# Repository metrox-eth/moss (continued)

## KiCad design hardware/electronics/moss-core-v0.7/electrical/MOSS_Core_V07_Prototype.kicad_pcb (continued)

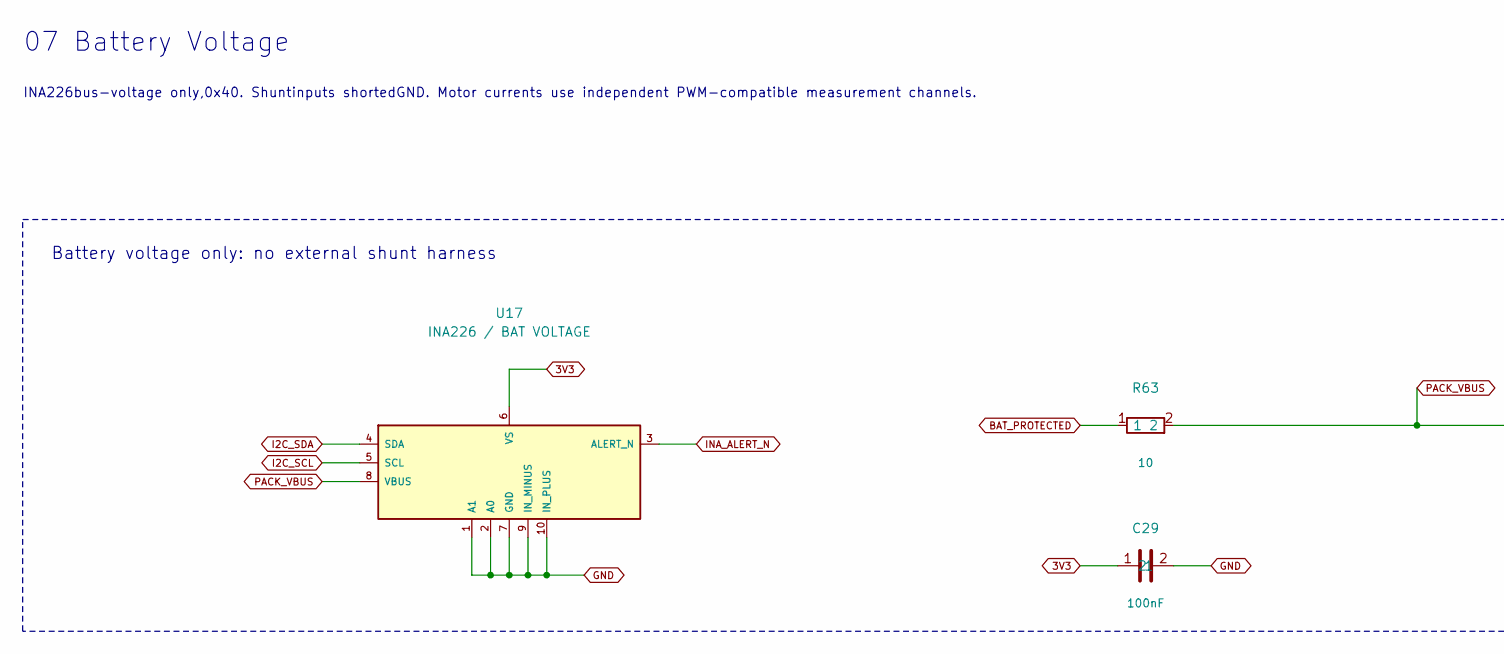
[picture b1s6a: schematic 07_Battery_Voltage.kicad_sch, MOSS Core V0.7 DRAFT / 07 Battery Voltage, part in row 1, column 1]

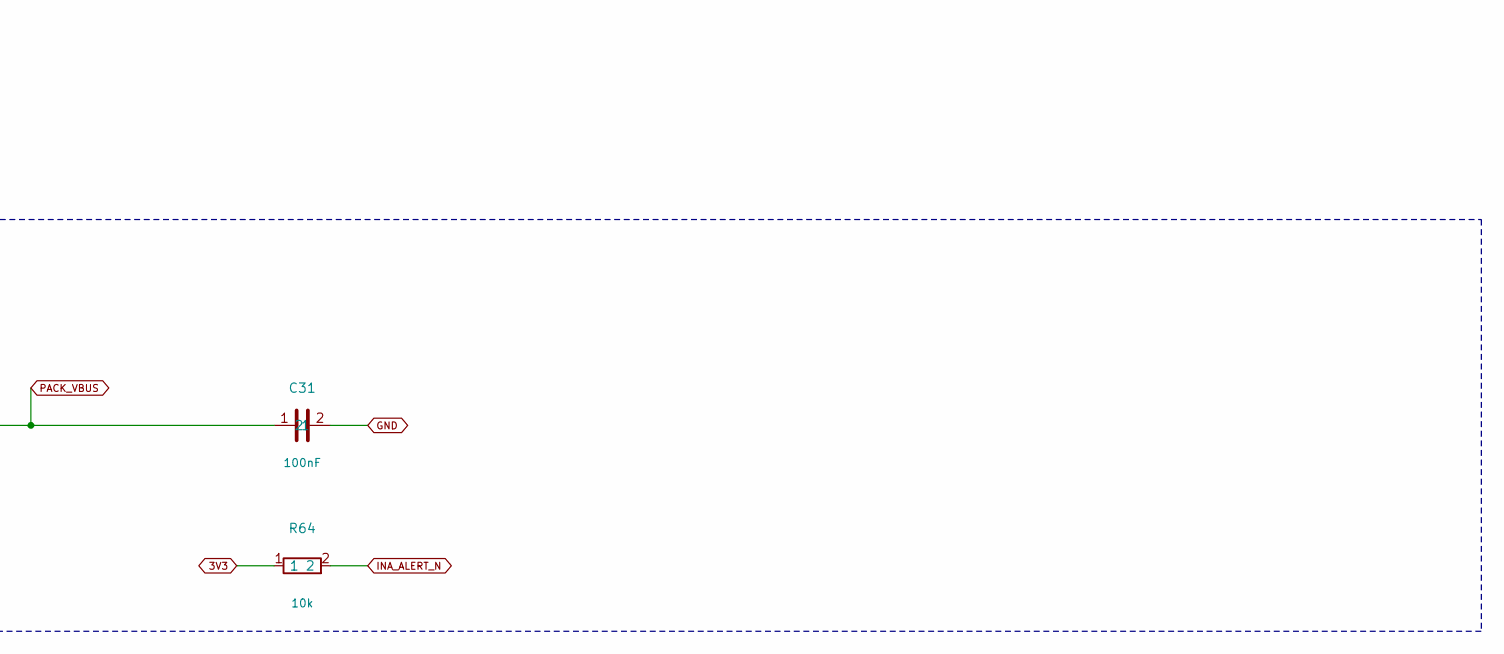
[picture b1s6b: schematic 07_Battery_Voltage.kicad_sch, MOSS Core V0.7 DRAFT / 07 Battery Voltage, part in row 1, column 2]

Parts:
C29: 100nF; Capacitor_SMD_C_0603_1608Metric; MPN GRM188R71C104KA01D
C31: 100nF; Capacitor_SMD_C_0603_1608Metric; MPN GRM188R71H104KA93D
R63: 10; Resistor_SMD_R_0603_1608Metric; MPN RC0603FR-0710RL
R64: 10k; Resistor_SMD_R_0603_1608Metric; MPN RC0603FR-0710KL
U17: INA226 / BAT VOLTAGE; Package_SO_MSOP-10_3x3mm_P0.5mm; MPN INA226AIDGSR

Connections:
3V3: C29.1, R64.1, U17.6 (VS); also elsewhere on the board
BAT_PROTECTED: R63.1; also elsewhere on the board
GND: C29.2, C31.2, U17.1 (A1), U17.2 (A0), U17.7 (GND), U17.9 (IN_MINUS), U17.10 (IN_PLUS); also elsewhere on the board
I2C_SCL: U17.5 (SCL); also elsewhere on the board
I2C_SDA: U17.4 (SDA); also elsewhere on the board
INA_ALERT_N: R64.2, U17.3 (ALERT_N)
PACK_VBUS: C31.1, R63.2, U17.8 (VBUS)

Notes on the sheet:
07 Battery Voltage
INA226bus-voltage only,0x40. Shuntinputs shortedGND. Motor currents use independent PWM-compatible measurement channels.
Battery voltage only: no external shunt harness

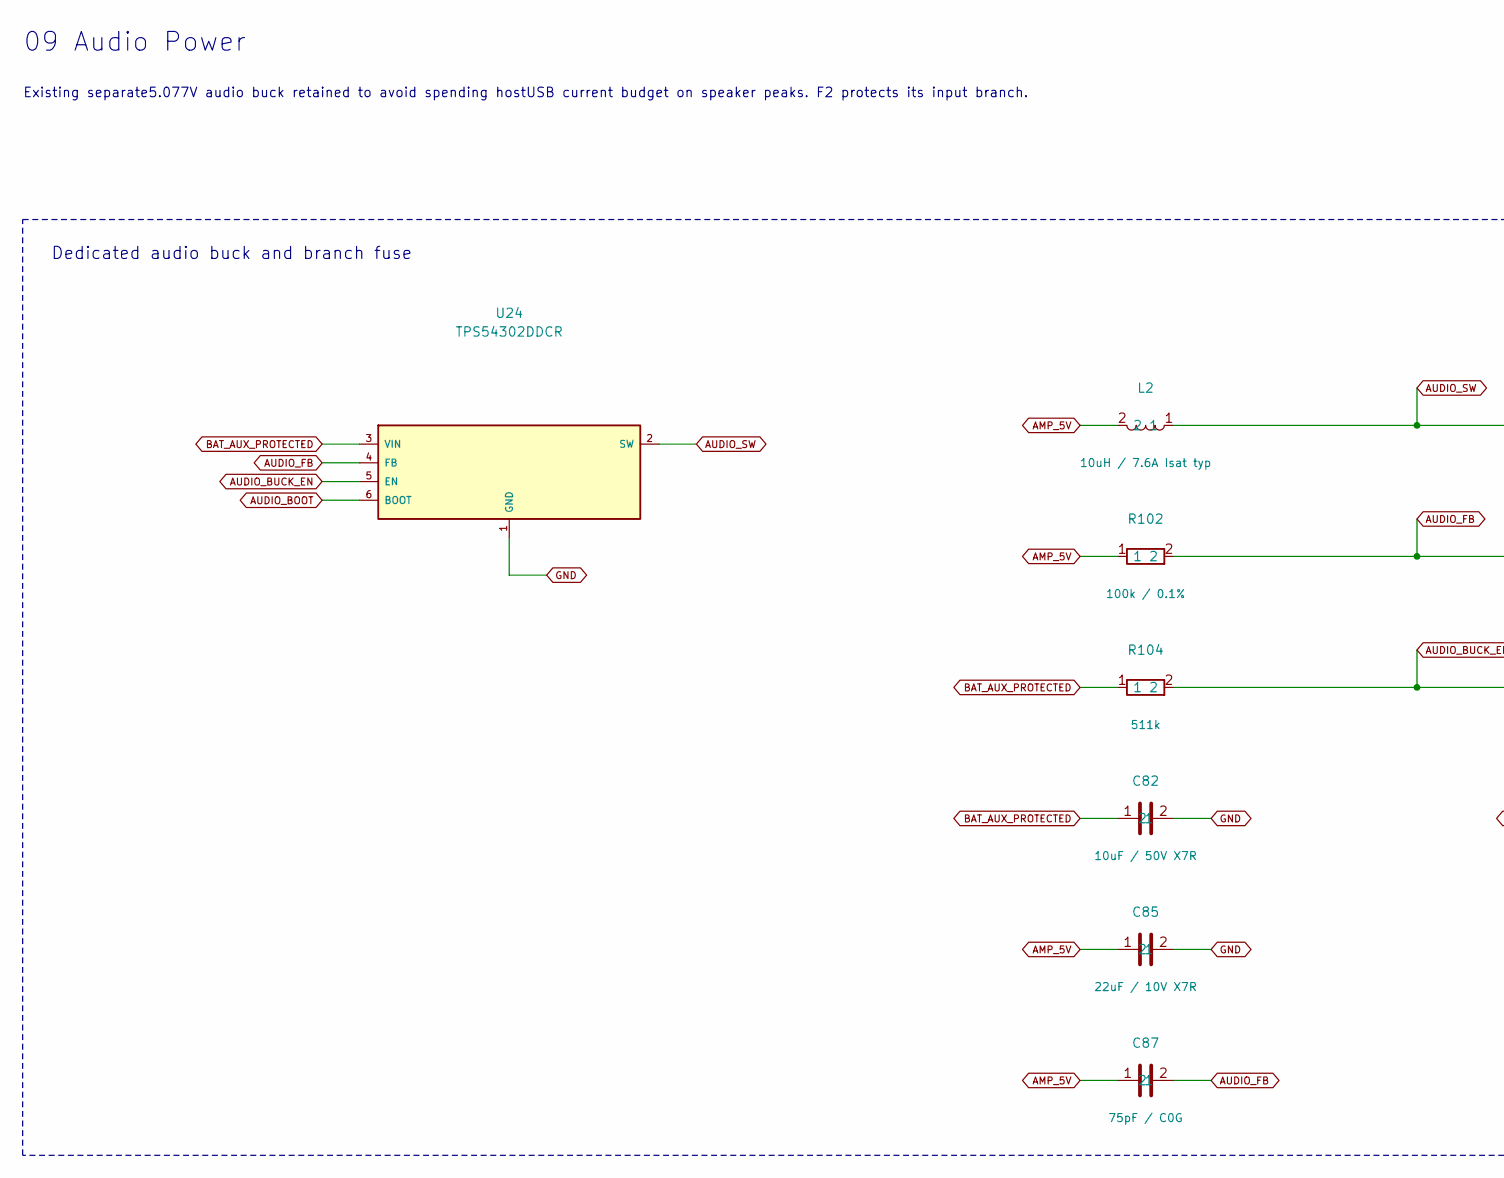
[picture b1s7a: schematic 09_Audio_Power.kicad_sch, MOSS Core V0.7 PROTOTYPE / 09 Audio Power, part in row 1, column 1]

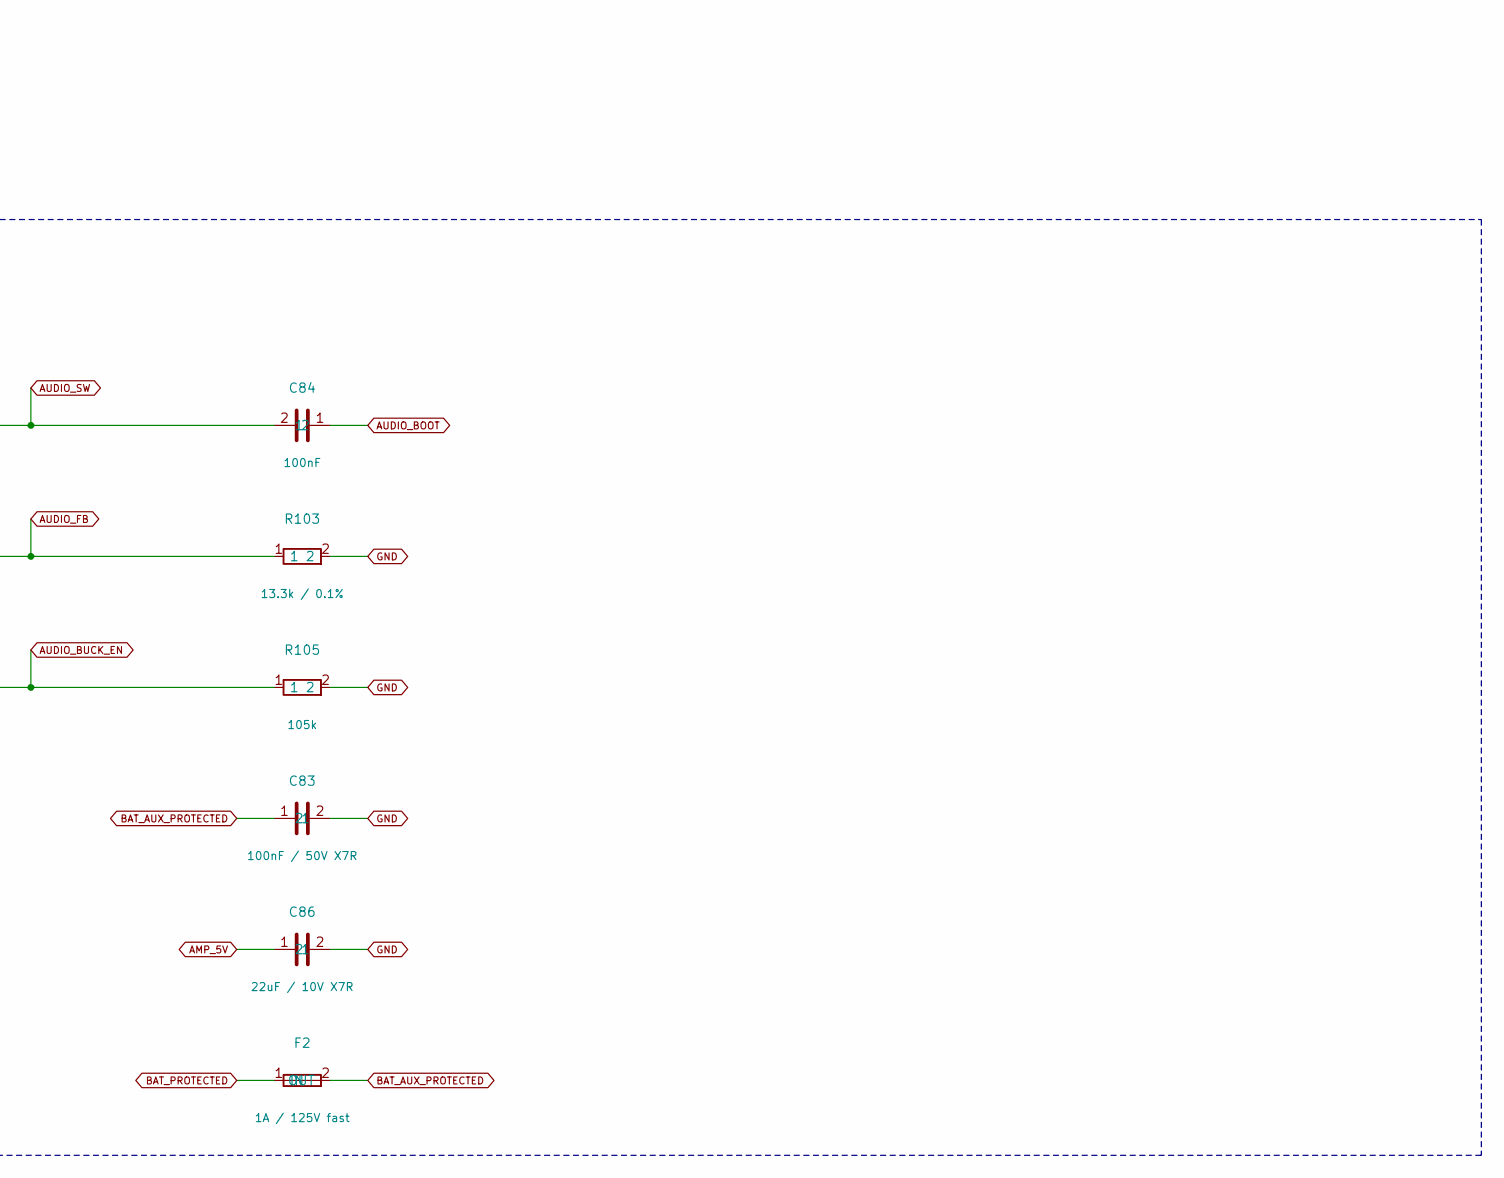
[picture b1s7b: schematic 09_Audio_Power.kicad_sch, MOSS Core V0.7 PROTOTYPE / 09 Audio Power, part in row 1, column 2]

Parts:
C82: 10uF / 50V X7R; Capacitor_SMD_C_1210_3225Metric; MPN GRM32ER71H106KA12L
C83: 100nF / 50V X7R; Capacitor_SMD_C_0805_2012Metric; MPN C0805C104K5RACTU
C84: 100nF; Capacitor_SMD_C_0603_1608Metric; MPN GRM188R71C104KA01D
C85, C86: 22uF / 10V X7R; Capacitor_SMD_C_1206_3216Metric; MPN GRM31CR71A226KE15L
C87: 75pF / C0G; Capacitor_SMD_C_0603_1608Metric; MPN GRM1885C1H750JA01D
F2: 1A / 125V fast; Fuse_Littelfuse_0451_Nano2; MPN 0451001.MRL
L2: 10uH / 7.6A Isat typ; Inductor_SMD_L_Bourns_SRP6060FA; MPN SRP6060FA-100M
R102: 100k / 0.1%; Resistor_SMD_R_0603_1608Metric; MPN RT0603BRD07100KL
R103: 13.3k / 0.1%; Resistor_SMD_R_0603_1608Metric; MPN RT0603BRD0713K3L
R104: 511k; Resistor_SMD_R_0603_1608Metric; MPN RC0603FR-07511KL
R105: 105k; Resistor_SMD_R_0603_1608Metric; MPN RC0603FR-07105KL
U24: TPS54302DDCR; Package_TO_SOT_SMD_SOT-23-6; MPN TPS54302DDCR

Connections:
AMP_5V: C85.1, C86.1, C87.1, L2.2, R102.1; also elsewhere on the board
AUDIO_BOOT: C84.1, U24.6 (BOOT)
AUDIO_BUCK_EN: R104.2, R105.1, U24.5 (EN)
AUDIO_FB: C87.2, R102.2, R103.1, U24.4 (FB)
AUDIO_SW: C84.2, L2.1, U24.2 (SW)
BAT_AUX_PROTECTED: C82.1, C83.1, F2.2 (OUT), R104.1, U24.3 (VIN)
BAT_PROTECTED: F2.1 (IN); also elsewhere on the board
GND: C82.2, C83.2, C85.2, C86.2, R103.2, R105.2, U24.1 (GND); also elsewhere on the board

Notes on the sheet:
09 Audio Power
Existing separate5.077V audio buck retained to avoid spending hostUSB current budget on speaker peaks. F2 protects its input branch.
Dedicated audio buck and branch fuse

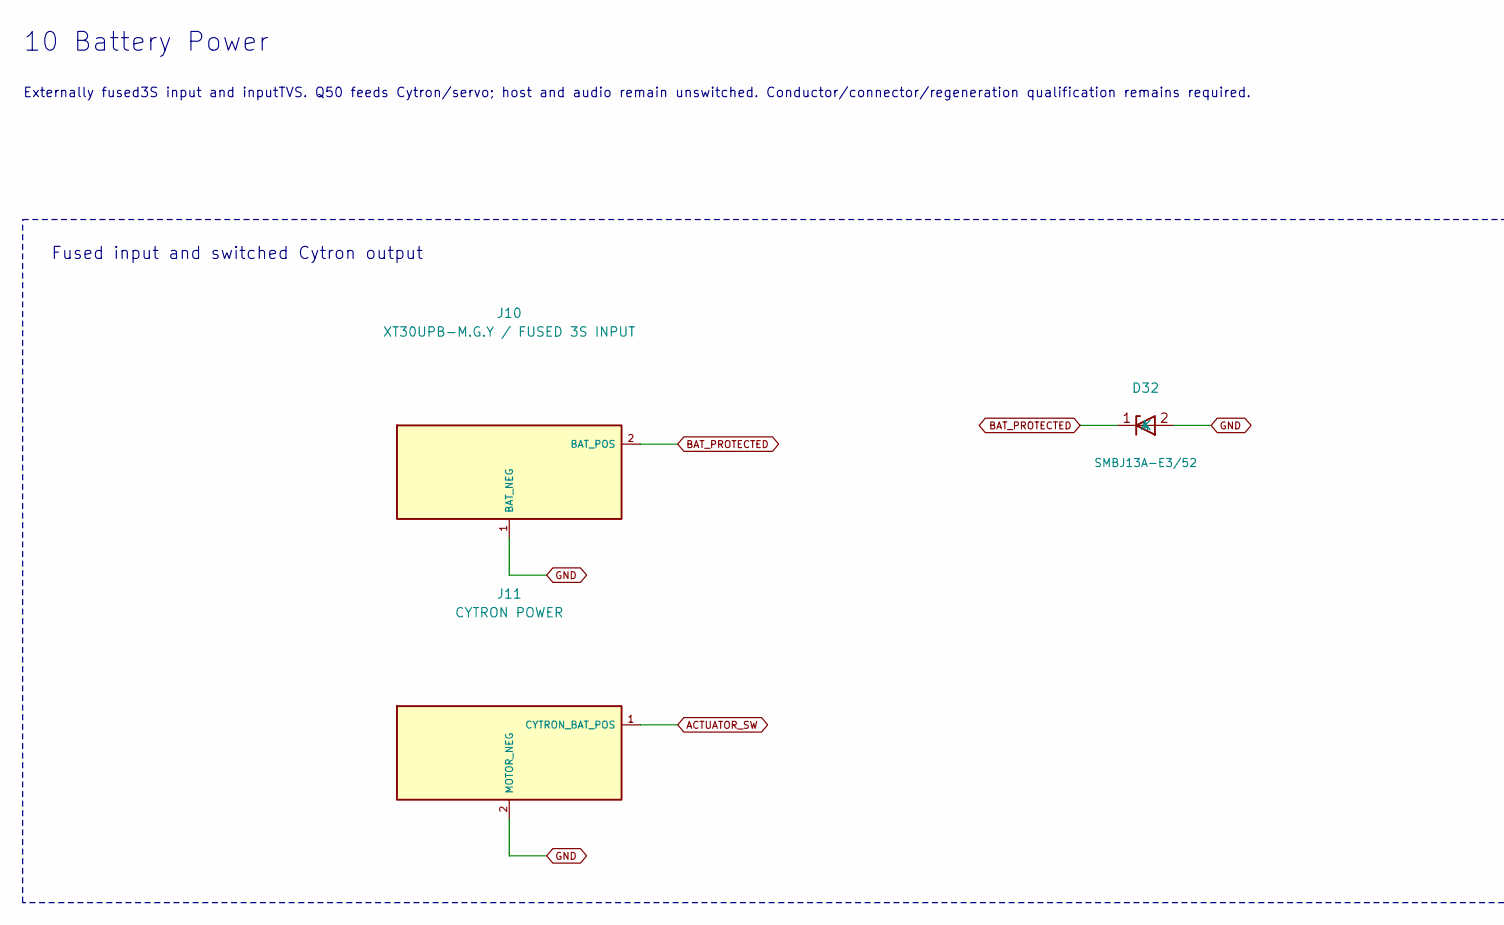
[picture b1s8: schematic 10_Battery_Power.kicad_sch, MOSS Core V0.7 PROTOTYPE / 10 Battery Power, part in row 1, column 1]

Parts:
D32: SMBJ13A-E3/52; Diode_SMD_D_SMB; MPN SMBJ13A-E3/52
J10: XT30UPB-M.G.Y / FUSED 3S INPUT; Connector_AMASS_AMASS_XT30UPB-M_1x02_P5.0mm_Vertical; MPN XT30UPB-M.G.Y
J11: CYTRON POWER; TerminalBlock_Phoenix_TerminalBlock_Phoenix_MKDS-1,5-2-5.08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; MPN 1715721

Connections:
ACTUATOR_SW: J11.1 (CYTRON_BAT_POS); also elsewhere on the board
BAT_PROTECTED: D32.1 (K), J10.2 (BAT_POS); also elsewhere on the board
GND: D32.2 (A), J10.1 (BAT_NEG), J11.2 (MOTOR_NEG); also elsewhere on the board

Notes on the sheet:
10 Battery Power
Externally fused3S input and inputTVS. Q50 feeds Cytron/servo; host and audio remain unswitched. Conductor/connector/regeneration qualification remains required.
Fused input and switched Cytron output

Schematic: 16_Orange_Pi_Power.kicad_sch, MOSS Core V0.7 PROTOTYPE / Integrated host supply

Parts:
C140: 220uF 10V polymer; Capacitor_SMD_CP_Elec_6.3x5.9; MPN 10SVPE220M
C141: 100nF 50V X7R; Capacitor_SMD_C_0603_1608Metric; MPN GRM188R71H104KA93D
C142: 10uF 25V X7R; Capacitor_SMD_C_1206_3216Metric; MPN GRM31CR71E106KA12L
C160: 22uF / 25V X7R; Capacitor_SMD_C_1210_3225Metric; MPN GRM32ER71E226KE15L
C162, C163, C167: 100nF / 50V X7R; Capacitor_SMD_C_0603_1608Metric; MPN GRM188R71H104KA93D
C164, C165: 22uF / 10V X7R; Capacitor_SMD_C_1206_3216Metric; MPN GRM31CR71A226KE15L
C166: 1uF / 10V; Capacitor_SMD_C_0603_1608Metric; MPN GRM188R61A105KA61D
C168: 33nF / 50V X7R; Capacitor_SMD_C_0603_1608Metric; MPN GRM188R71H333KA61D
C169: 390pF / C0G; Capacitor_SMD_C_0603_1608Metric; MPN GRM1885C1H391JA01D
F1: 3.15A / compact host input fuse; Fuse_Fuse_Littelfuse-NANO2-885; MPN 08853.15DR
J20: 5V3A OUT TO ORANGE PI; Connector_USB_USB_C_Receptacle_GCT_USB4105-xx-A_16P_TopMnt_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; MPN USB4105-GF-A
L3: 10uH; Inductor_SMD_L_Bourns_SRP6060FA; MPN SRP6060FA-100M
R200: 100k 1% 100ppm; Resistor_SMD_R_0603_1608Metric; MPN RC0603FR-07100KL
R210: 499k; Resistor_SMD_R_0603_1608Metric; MPN RC0603FR-07499KL
R211: 100k; Resistor_SMD_R_0603_1608Metric; MPN RC0603FR-07100KL
R212: 4.7; Resistor_SMD_R_0603_1608Metric; MPN RC0603FR-074R7L
R213: 53.6k; Resistor_SMD_R_0603_1608Metric; MPN RC0603FR-0753K6L
R214: 10k; Resistor_SMD_R_0603_1608Metric; MPN RC0603FR-0710KL
R215: 845k; Resistor_SMD_R_0603_1608Metric; MPN RC0603FR-07845KL
U42: TPS25810RVCR / USB-C source3A; Package_DFN_QFN_Texas_RVC0020A_WQFN-20-1EP_3x4mm_P0.5mm_EP1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; MPN TPS25810RVCR
U60: MP9447GL-Z / integrated host buck; MOSS_Power_MP9447_QFN25_3x4; MPN MP9447GL-Z

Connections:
BAT_PROTECTED: F1.1; also elsewhere on the board
GND: C140.2, C141.2, C142.2, C160.2, C162.2, C163.2, C164.2, C165.2, C166.2, C168.2, J20.A1 (GND), J20.A12 (GND), J20.B1 (GND), J20.B12 (GND), J20.SH (SHIELD), R211.2, R214.2, U42.12 (GND), U42.21 (EP), U60.1 (AGND), U60.11 (PGND), U60.12 (PGND), U60.13 (PGND), U60.14 (PGND), U60.15 (PGND), U60.16 (PGND); also elsewhere on the board
HOST_5V: C142.1, J20.A4 (VBUS), J20.A9 (VBUS), J20.B4 (VBUS), J20.B9 (VBUS), U42.14 (OUT), U42.15 (OUT)
HOST_BST: R212.1, U60.7 (BST)
HOST_BST_CAP: C167.1, R212.2
HOST_BUCK_IN: C160.1, C162.1, C163.1, F1.2, R210.1, U60.8 (IN), U60.19 (IN), U60.21 (IN), U60.22 (IN), U60.23 (IN)
HOST_CC1: J20.A5 (CC1), U42.11 (CC1)
HOST_CC2: J20.B5 (CC2), U42.13 (CC2)
HOST_CC_REF: R200.1, U42.10 (REF)
HOST_CC_REF_RTN: R200.2, U42.9 (REF_RTN)
HOST_EN: R210.2, U60.5 (EN)
HOST_FB: C169.2, R213.2, R214.1, U60.3 (FB)
HOST_FREQ: R211.1, U60.2 (FREQ)
HOST_RAMP: C169.1, R215.2
HOST_SS: C168.1, U60.4 (SS)
HOST_SW: C167.2, L3.1, R215.1, U60.9 (SW), U60.10 (SW), U60.17 (SW), U60.18 (SW), U60.24 (SW), U60.25 (SW)
HOST_VCC: C166.1, U60.20 (VCC)
V5_HOST_RAW: C140.1, C141.1, C164.1, C165.1, L3.2, R213.1, U42.2 (IN1), U42.3 (IN1), U42.4 (IN2), U42.5 (AUX), U42.6 (EN), U42.7 (CHG), U42.8 (CHG_HI)

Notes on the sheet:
INTEGRATED HOST POWER / MP9447 / ENGINEERING CANDIDATE
3S battery -> F1 -> U60/L3 -> V5_HOST_RAW -> U42 -> HOST_5V -> J20. Keep VBUS and V5 separate.

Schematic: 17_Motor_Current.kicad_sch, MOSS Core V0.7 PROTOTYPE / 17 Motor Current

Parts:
C120, C123, C126: 100n 16V X7R; Capacitor_SMD_C_0603_1608Metric; MPN C0603C104K4RACTU
C121, C124: 2.2u 16V X7R; Capacitor_SMD_C_0805_2012Metric; MPN C0805C225K4RACTU
C122, C125: 1u 16V X7R; Capacitor_SMD_C_0603_1608Metric; MPN C0603C105K4RACTU
J12: L MOTOR SENSE LOOP; TerminalBlock_Phoenix_TerminalBlock_Phoenix_MKDS-1,5-2-5.08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; MPN 1715721
J13: R MOTOR SENSE LOOP; TerminalBlock_Phoenix_TerminalBlock_Phoenix_MKDS-1,5-2-5.08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; MPN 1715721
R180, R181: 2mR 1% 5W; MOSS_V07_CSS2H_2512K_Bourns; MPN CSS2H-2512K-2L00F
R182, R183: 470R 1%; Resistor_SMD_R_0603_1608Metric; MPN CRCW0603470RFKEA
U40, U41: INA240A2PWR; Package_SO_TSSOP-8_4.4x3mm_P0.65mm; MPN INA240A2PWR
U43: ADS1115IDGSR; Package_SO_MSOP-10_3x3mm_P0.5mm; MPN ADS1115IDGSR

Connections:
3V3: C120.1, C122.1, C123.1, C125.1, C126.1, U40.5 (VS), U40.7 (REF1), U41.5 (VS), U41.7 (REF1), U43.6 (AIN2), U43.8 (VDD); also elsewhere on the board
CURRENT_L_ADC: C121.1, R182.2, U43.4 (AIN0)
CURRENT_L_RAW: R182.1, U40.8 (OUT)
CURRENT_R_ADC: C124.1, R183.2, U43.5 (AIN1)
CURRENT_R_RAW: R183.1, U41.8 (OUT)
CYTRON_L_LEAD: J12.1 (FROM_CYTRON), R180.1 (I_FROM_CYTRON), U40.2 (IN+); also elsewhere on the board
CYTRON_R_LEAD: J13.1 (FROM_CYTRON), R181.1 (I_FROM_CYTRON), U41.2 (IN+); also elsewhere on the board
GND: C120.2, C121.2, C122.2, C123.2, C124.2, C125.2, C126.2, U40.4 (GND), U40.6 (REF2), U41.4 (GND), U41.6 (REF2), U43.1 (ADDR), U43.3 (GND), U43.7 (AIN3); also elsewhere on the board
I2C_SCL: U43.10 (SCL); also elsewhere on the board
I2C_SDA: U43.9 (SDA); also elsewhere on the board
MOTOR_L_LEAD: J12.2 (TO_MOTOR), R180.2 (I_TO_MOTOR), U40.3 (IN-); also elsewhere on the board
MOTOR_R_LEAD: J13.2 (TO_MOTOR), R181.2 (I_TO_MOTOR), U41.3 (IN-); also elsewhere on the board

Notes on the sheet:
17 Motor Current
Separate left/right in-linebidirectional motor currents; two shunts andPWM-rejecting amplifiers. ValidateADCcalibration,transients and thermal performance.
Left in-line winding current
Right in-line winding current
Digital ADC and reference supply measurement

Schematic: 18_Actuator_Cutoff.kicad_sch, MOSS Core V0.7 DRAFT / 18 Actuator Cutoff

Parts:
C150, C152: 10n; Capacitor_SMD_C_0603_1608Metric; MPN GRM188R71H103KA01D
C151: 100n; Capacitor_SMD_C_0603_1608Metric; MPN GRM188R71H104KA93D
C153: 1n; Capacitor_SMD_C_0603_1608Metric; MPN GRM188R71H102KA01D
D50: BZT52C12; Diode_SMD_D_SOD-123; MPN BZT52C12-E3-08
J8: E-STOP / SIGNAL ONLY; Connector_JST_JST_SH_BM06B-SRSS-TB_1x06-1MP_P1.00mm_Vertical; MPN BM06B-SRSS-TB(LF)(SN)
Q50: SiRA99DP; Package_SO_PowerPAK_SO-8_Single; MPN SiRA99DP-T1-GE3
Q51, Q52: BSS138BK; Package_TO_SOT_SMD_SOT-23; MPN BSS138BK,215
R220, R226: 1k; Resistor_SMD_R_1206_3216Metric; MPN RC1206FR-071KL
R221: 330; Resistor_SMD_R_1206_3216Metric; MPN RC1206FR-07330RL
R222: 1k; Resistor_SMD_R_0603_1608Metric; MPN RC0603FR-071KL
R223, R227: 10k; Resistor_SMD_R_0603_1608Metric; MPN RC0603FR-0710KL
R224: 47; Resistor_SMD_R_0603_1608Metric; MPN RC0603FR-0747RL
R225: 470; Resistor_SMD_R_0603_1608Metric; MPN RC0603FR-07470RL
U50: SN74LVC1G14; Package_TO_SOT_SMD_SOT-23-5; MPN SN74LVC1G14DBVR

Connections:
3V3: C151.1, R224.1, U50.5 (VCC); also elsewhere on the board
ACTUATOR_SW: Q50.5 (D5-8_PAD), R226.1; also elsewhere on the board
ACT_GATE: C152.2, D50.2 (A), Q50.4 (G), R220.2, R221.1
ACT_POWER_ENABLE: R222.1; also elsewhere on the board
ACT_SINK_GATE: C153.1, Q51.1 (G), R222.2, R223.1
BAT_PROTECTED: C152.1, D50.1 (K), Q50.1 (S1), Q50.2 (S2), Q50.3 (S3), R220.1; also elsewhere on the board
ESTOP_ACTIVE: Q52.1 (G), R227.1, U50.4 (Y); also elsewhere on the board
ESTOP_CUT_RETURN: J8.2 (CUT_RETURN), Q51.3 (D)
ESTOP_CUT_SOURCE: J8.1 (CUT_SOURCE), R221.2
ESTOP_STATUS_RAW: C150.1, J8.6 (STATUS_RETURN), R225.1, U50.2 (A)
ESTOP_STATUS_SOURCE: J8.5 (STATUS_SOURCE), R224.2
GND: C150.2, C151.2, C153.2, J8.MP (MOUNT), Q51.2 (S), Q52.2 (S), R223.2, R225.2, R226.2, R227.2, U50.3 (GND); also elsewhere on the board
WD_RESET_N: Q52.3 (D); also elsewhere on the board

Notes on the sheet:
18 Actuator Cutoff
One physical NC opens Q50 gate sink regardless of MCU command. Second NC requests MCU reset; release requires fresh manual arming. Unknown actual button terminal orientation must be verified. Single MOSFET is not redundant or safety-certified; inrush, stored energy and regeneration require bench te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
High-side actuator switch / NC contact dominates gate
MCU arm request / default off
Two NC contacts / signal harness only
Auxiliary stop contact resets controller

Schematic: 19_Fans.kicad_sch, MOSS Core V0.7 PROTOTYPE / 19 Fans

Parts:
F3: 1A / 125V fast; Fuse_Littelfuse_0451_Nano2; MPN 0451001.MRL
J14: FAN 1 / 3S; Connector_JST_JST_XH_B2B-XH-A_1x02_P2.50mm_Vertical; MPN B2B-XH-A(LF)(SN)
J15: FAN 2 / 3S; Connector_JST_JST_XH_B2B-XH-A_1x02_P2.50mm_Vertical; MPN B2B-XH-A(LF)(SN)

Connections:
BAT_PROTECTED: F3.1 (IN); also elsewhere on the board
FAN_3S: F3.2 (OUT), J14.1 (FAN_POS), J15.1 (FAN_POS)
GND: J14.2 (FAN_NEG), J15.2 (FAN_NEG); also elsewhere on the board

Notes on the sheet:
19 Fans
Two12V nominal3010 fans,common1A fuse upstream of Q50;0.2A combined assumed,not measured. Verify XH mate/polarity,voltage/startup and wire limits.
Battery-fed fans / powered during actuator stop

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
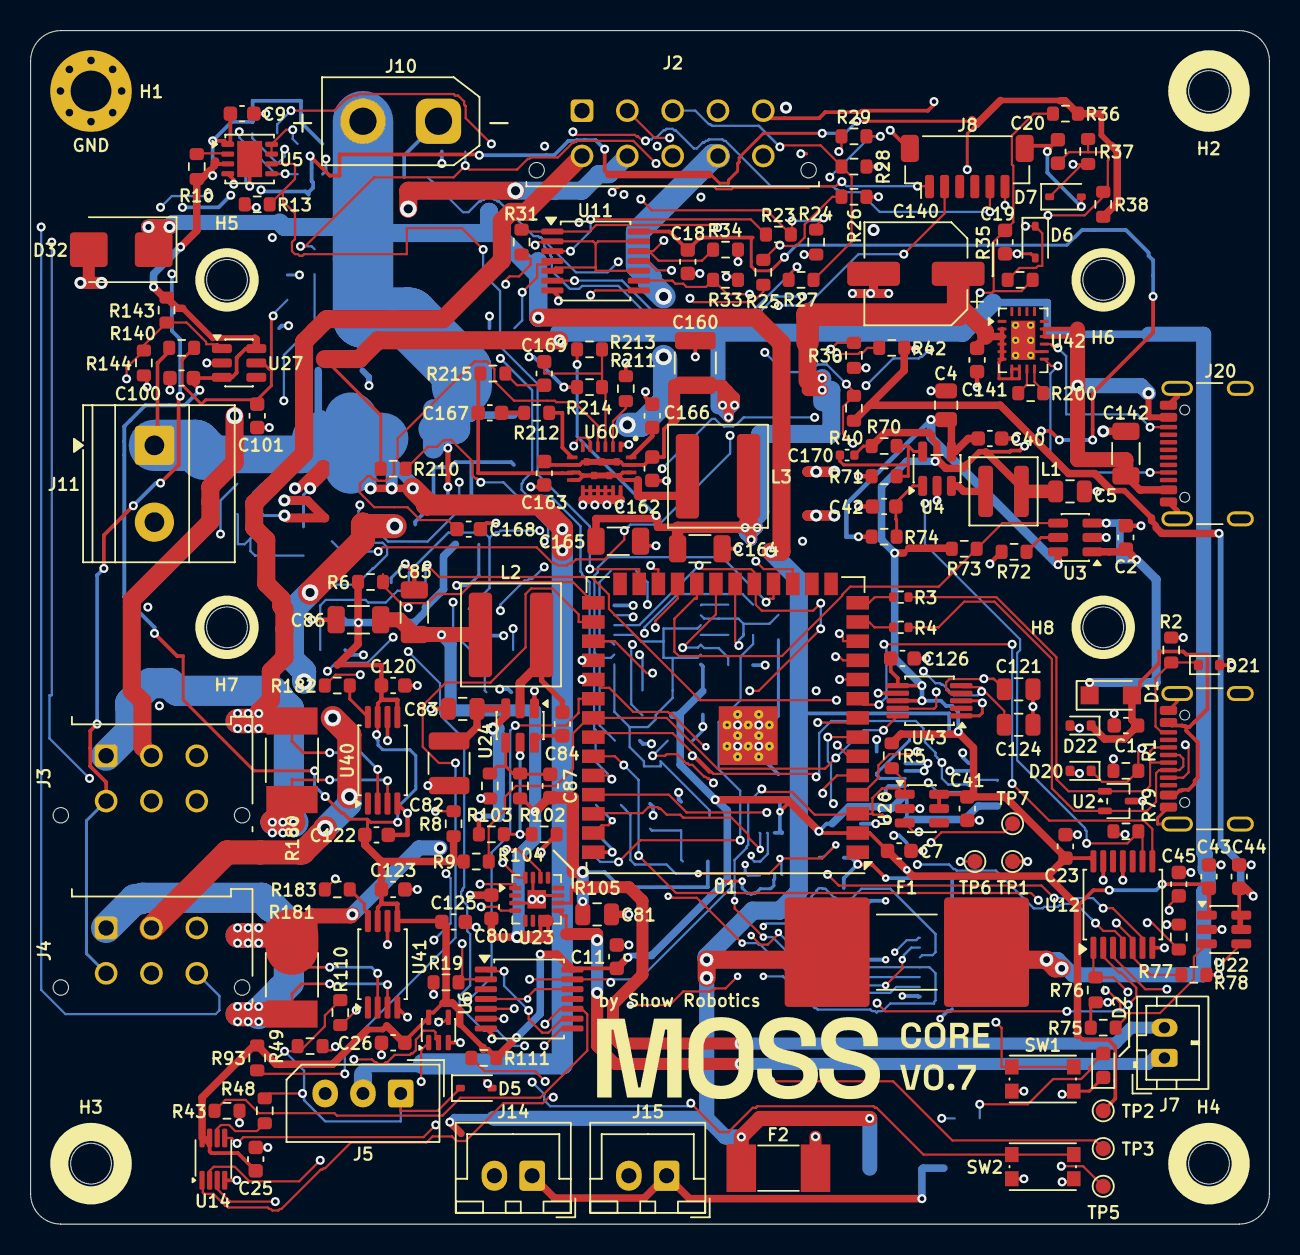
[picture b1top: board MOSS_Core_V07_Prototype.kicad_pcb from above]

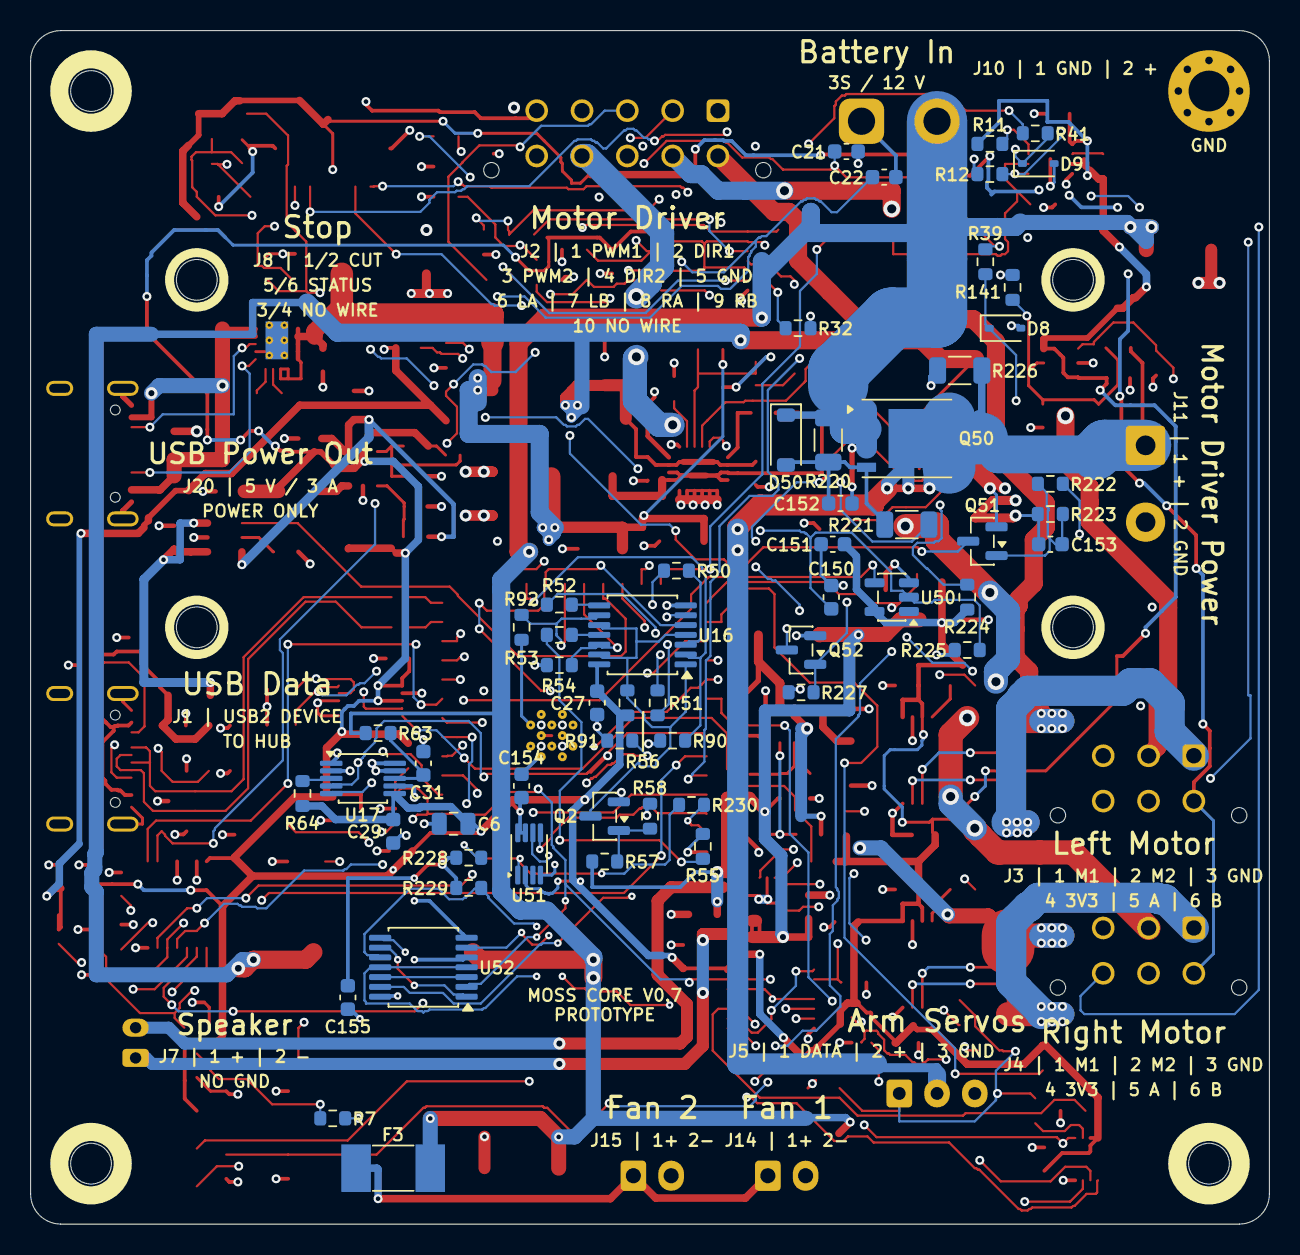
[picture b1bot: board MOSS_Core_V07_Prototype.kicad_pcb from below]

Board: 4 copper layers, 82.0 x 79.0 mm, 230 parts (57 on the bottom side), 133 nets.

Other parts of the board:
C154, C155: 100nF; Capacitor_SMD_C_0603_1608Metric
C170: 6.8pF C0G 50V; Capacitor_SMD_C_0402_1005Metric
R228: 10k; Resistor_SMD_R_0603_1608Metric
R229: 100k; Resistor_SMD_R_0603_1608Metric
R230: 100; Resistor_SMD_R_0603_1608Metric
U51: SN74LVC1G74DCUR; Package_SO_VSSOP-8_2.3x2mm_P0.5mm
U52: SN74HCS11PWR; Package_SO_TSSOP-14_4.4x5mm_P0.65mm

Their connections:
3V3: C154.1, C155.1, C170.1, U51.2, U51.7, U51.8, U52.5, U52.14; also elsewhere on the board
ACT_POWER_ENABLE: U52.4, U52.11; also elsewhere on the board
ARM_CLEAR_BASE: U52.3, U52.12
ARM_CLEAR_N: U51.6, U52.6
ARM_COMMIT: R230.1; also elsewhere on the board
ARM_COMMIT_CLK: R228.1, R230.2, U51.1
ARM_LATCHED: R229.1, U51.5, U52.10; also elsewhere on the board
BUCK_FB: C170.2; also elsewhere on the board
GND: C154.2, C155.2, R228.2, R229.2, U51.4, U52.7; also elsewhere on the board
RESET_N: U52.2; also elsewhere on the board
WD_ENABLE: U52.13; also elsewhere on the board

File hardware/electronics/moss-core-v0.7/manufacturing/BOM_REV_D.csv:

Designator,Quantity,Manufacturer Part Number,Value,Footprint,Manufacturer,Assembly notes
"C1,C2,C43,C44",4,GRM188R61A105KA61D,1uF,Capacitor_SMD:C_0603_1608Metric,,
C4,1,GRM21BR71A475KA73L,4.7uF,Capacitor_SMD:C_0805_2012Metric,,
"C5,C6",2,GRM21BR71A106KA73L,10uF,Capacitor_SMD:C_0805_2012Metric,,
"C7,C9,C11,C18,C23,C25,C26,C27,C29,C40,C41,C42,C80,C84,C100",15,GRM188R71C104KA01D,GRM188R71C104KA01D,Capacitor_SMD:C_0603_1608Metric,,
"C19,C20,C21,C22",4,GRM1885C1H101JA01D,100pF,Capacitor_SMD:C_0603_1608Metric,,
"C31,C141,C151",3,GRM188R71H104KA93D,GRM188R71H104KA93D,Capacitor_SMD:C_0603_1608Metric,,
"C45,C150,C152",3,GRM188R71H103KA01D,GRM188R71H103KA01D,Capacitor_SMD:C_0603_1608Metric,,
C81,1,GRM21BR71A106KE51L,10uF / 10V X7R,Capacitor_SMD:C_0805_2012Metric,,
C82,1,GRM32ER71H106KA12L,10uF / 50V X7R,Capacitor_SMD:C_1210_3225Metric,,
C83,1,C0805C104K5RACTU,100nF / 50V X7R,Capacitor_SMD:C_0805_2012Metric,,
"C85,C86",2,GRM31CR71A226KE15L,22uF / 10V X7R,Capacitor_SMD:C_1206_3216Metric,,
C87,1,GRM1885C1H750JA01D,75pF / C0G,Capacitor_SMD:C_0603_1608Metric,,
C101,1,GRM1885C1H102JA01D,1n,Capacitor_SMD:C_0603_1608Metric,,
"C120,C123,C126",3,C0603C104K4RACTU,100n 16V X7R,Capacitor_SMD:C_0603_1608Metric,,
"C121,C124",2,C0805C225K4RACTU,2.2u 16V X7R,Capacitor_SMD:C_0805_2012Metric,,
"C122,C125",2,C0603C105K4RACTU,1u 16V X7R,Capacitor_SMD:C_0603_1608Metric,,
C140,1,10SVPE220M,220uF 10V polymer,Capacitor_SMD:CP_Elec_6.3x5.9,,
C142,1,GRM31CR71E106KA12L,10uF 25V X7R,Capacitor_SMD:C_1206_3216Metric,,
C153,1,GRM188R71H102KA01D,1n,Capacitor_SMD:C_0603_1608Metric,,
D1,1,"PMEG2010ER,115",PMEG2010ER,Diode_SMD:Nexperia_CFP3_SOD-123W,,
D2,1,LTST-C190KGKT,GREEN,LED_SMD:LED_0603_1608Metric,,
"D5,D6,D7,D8,D9",5,"PESD5V0S1BA,115",PESD5V0S1BA,Diode_SMD:D_SOD-323,,
"D20,D21,D22",3,TPD1E10B06DYAR,TPD1E10B06DYAR,Diode_SMD:D_SOD-523,,
D32,1,SMBJ13A-E3/52,SMBJ13A-E3/52,Diode_SMD:D_SMB,,
D50,1,BZT52C12-E3-08,BZT52C12,Diode_SMD:D_SOD-123,,
F1,1,08853.15DR,3.15A / compact host input fuse,Fuse:Fuse_Littelfuse-NANO2-885,Littelfuse,
"F2,F3",2,0451001.MRL,1A / 125V fast,Fuse:Littelfuse_0451_Nano2,,
"J1,J20",2,USB4105-GF-A,USB4105-GF-A,Connector_USB:USB_C_Receptacle_GCT_USB4105-xx-A_16P_TopMnt_Horizontal,,
J2,1,SM05B-GHS-TB(LF)(SN),CYTRON MDD10A SIGNAL,Connector_JST:JST_GH_SM05B-GHS-TB_1x05-1MP_P1.25mm_Horizontal,,
"J3,J4",2,SM04B-GHS-TB(LF)(SN),SM04B-GHS-TB(LF)(SN),Connector_JST:JST_GH_SM04B-GHS-TB_1x04-1MP_P1.25mm_Horizontal,,
J5,1,22-05-7035,ARM / DATA V+ GND,Connector_Molex:Molex_SPOX_5268-03A_1x03_P2.50mm_Horizontal,,
J7,1,S2B-PH-K-S(LF)(SN),SPEAKER / 4 ohm 3 W,Connector_JST:JST_PH_S2B-PH-K_1x02_P2.00mm_Horizontal,,
J8,1,BM06B-SRSS-TB(LF)(SN),E-STOP / SIGNAL ONLY,Connector_JST:JST_SH_BM06B-SRSS-TB_1x06-1MP_P1.00mm_Vertical,,
J10,1,XT30PW-M,XT30PW-M / FUSED 3S INPUT,Connector_AMASS:AMASS_XT30PW-M_1x02_P2.50mm_Horizontal_EdgeEntry,AMASS,
"J11,J12,J13",3,1715721,1715721,"TerminalBlock_Phoenix:TerminalBlock_Phoenix_MKDS-1,5-2-5.08_1x02_P5.08mm_Horizontal",,
"J14,J15",2,B2B-XH-A(LF)(SN),B2B-XH-A(LF)(SN),Connector_JST:JST_XH_B2B-XH-A_1x02_P2.50mm_Vertical,JST,
L1,1,XAL4020-222MEC,2.2uH,Inductor_SMD:L_Coilcraft_XAL4020-XXX,,
L2,1,SRP6060FA-100M,10uH / 7.6A Isat typ,Inductor_SMD:L_Bourns_SRP6060FA,,
MOD1,1,29035,DC5-36-TO-DC3V3-5 / 5V,MOSS_Power:Waveshare_DC5_36_TO_DC3V3_5_SMD_33x16mm_HandSolder,Waveshare,PCBWay if sourcing/assembly accepted
Q2,1,"MMBT3904,215",MMBT3904,Package_TO_SOT_SMD:SOT-23,,
Q50,1,SiRA99DP-T1-GE3,SiRA99DP,Package_SO:PowerPAK_SO-8_Single,,
"Q51,Q52",2,"BSS138BK,215",BSS138BK,Package_TO_SOT_SMD:SOT-23,,
"R1,R2",2,RC0603FR-075K1L,5.1k,Resistor_SMD:R_0603_1608Metric,,
"R3,R4",2,RC0402FR-0722RL,22,Resistor_SMD:R_0402_1005Metric,,
"R5,R6,R10,R11,R12,R13,R19,R24,R26,R28,R30,R36,R38,R40,R42,R43,R54,R56,R58,R64,R110,R111,R143,R223,R227",25,RC0603FR-0710KL,10k,Resistor_SMD:R_0603_1608Metric,,
"R7,R35,R37,R39,R41,R49,R222",7,RC0603FR-071KL,1k,Resistor_SMD:R_0603_1608Metric,,
"R8,R9",2,RC0603FR-074K7L,4.7k,Resistor_SMD:R_0603_1608Metric,,
"R23,R25,R27,R29",4,RC0603FR-07100RL,100,Resistor_SMD:R_0603_1608Metric,,
"R31,R32,R33,R34,R73,R75,R90,R91,R92,R93",10,RC0603FR-0747KL,47k,Resistor_SMD:R_0603_1608Metric,,
"R48,R50,R51,R52,R224",5,RC0603FR-0747RL,47,Resistor_SMD:R_0603_1608Metric,,
R53,1,RC0603FR-072K2L,2.2k,Resistor_SMD:R_0603_1608Metric,,
"R55,R74,R76,R77,R78,R79,R144,R200",8,RC0603FR-07100KL,RC0603FR-07100KL,Resistor_SMD:R_0603_1608Metric,,
R57,1,RC0603FR-0722KL,22k,Resistor_SMD:R_0603_1608Metric,,
R63,1,RC0603FR-0710RL,10,Resistor_SMD:R_0603_1608Metric,,
R70,1,RT0603BRD07464KL,464k,Resistor_SMD:R_0603_1608Metric,,
"R71,R102",2,RT0603BRD07100KL,RT0603BRD07100KL,Resistor_SMD:R_0603_1608Metric,,
R72,1,RC0603FR-0760K4L,60.4k,Resistor_SMD:R_0603_1608Metric,,
R103,1,RT0603BRD0713K3L,13.3k / 0.1%,Resistor_SMD:R_0603_1608Metric,,
R104,1,RC0603FR-07511KL,511k,Resistor_SMD:R_0603_1608Metric,,
R105,1,RC0603FR-07105KL,105k,Resistor_SMD:R_0603_1608Metric,,
R140,1,RT0603BRD07174KL,174k,Resistor_SMD:R_0603_1608Metric,,
R141,1,RT0603BRD0710KL,10k,Resistor_SMD:R_0603_1608Metric,,
"R180,R181",2,CSS2H-2512K-2L00F,2mR 1% 5W,MOSS_V07:CSS2H_2512K_Bourns,,
"R182,R183",2,CRCW0603470RFKEA,470R 1%,Resistor_SMD:R_0603_1608Metric,,
"R220,R226",2,RC1206FR-071KL,1k,Resistor_SMD:R_1206_3216Metric,,
R221,1,RC1206FR-07330RL,330,Resistor_SMD:R_1206_3216Metric,,
R225,1,RC0603FR-07470RL,470,Resistor_SMD:R_0603_1608Metric,,
"SW1,SW2",2,KMR221NGLFS,KMR221NGLFS,Button_Switch_SMD:SW_Push_1P1T_NO_CK_KMR2,C&K,
U1,1,ESP32-S3-WROOM-1U-N8,ESP32-S3-WROOM-1U-N8,RF_Module:ESP32-S3-WROOM-1U,,
U2,1,TPD2E2U06DCKR,TPD2E2U06DCKR,Package_TO_SOT_SMD:SOT-323_SC-70,,
U3,1,TPS2553DBVR,TPS2553DBVR,Package_TO_SOT_SMD:SOT-23-6,,
U4,1,TLV62569DBVR,TLV62569DBVR,Package_TO_SOT_SMD:SOT-23-5,,
U5,1,TPS3431SDRBR,TPS3431SDRBR,Package_SON:VSON-8-1EP_3x3mm_P0.65mm_EP1.65x2.4mm,,
U6,1,SN74HCS21PWR,SN74HCS21PWR,Package_SO:TSSOP-14_4.4x5mm_P0.65mm,,
U11,1,74LV08APWJ,74LV08APWJ,Package_SO:TSSOP-14_4.4x5mm_P0.65mm,,
U12,1,SN74LVC14APWR,SN74LVC14APWR,Package_SO:TSSOP-14_4.4x5mm_P0.65mm,,
U14,1,SN74LVC2G126DCUR,SN74LVC2G126DCUR,Package_SO:VSSOP-8_2.3x2mm_P0.5mm,,
U15,1,SN74LVC1G126DCKR,SN74LVC1G126DCKR,Package_TO_SOT_SMD:SOT-353_SC-70-5,,
U16,1,SN74LVC125APWR,SN74LVC125APWR,Package_SO:TSSOP-14_4.4x5mm_P0.65mm,,
U17,1,INA226AIDGSR,INA226 / BAT VOLTAGE,Package_SO:MSOP-10_3x3mm_P0.5mm,,
U20,1,TPS3808G33DBVR,TPS3808G33DBVR,Package_TO_SOT_SMD:SOT-23-6,,
U22,1,TPS22918DBVR,TPS22918DBVR,Package_TO_SOT_SMD:SOT-23-6,,
U23,1,MAX98357AETE+T,MAX98357AETE+T,Package_DFN_QFN:MAX98357A_T1633_4_90_0031,,
U24,1,TPS54302DDCR,TPS54302DDCR,Package_TO_SOT_SMD:SOT-23-6,,
U27,1,TPS3808G01DBVR,TPS3808G01DBVR,Package_TO_SOT_SMD:SOT-23-6,,
"U40,U41",2,INA240A2PWR,INA240A2PWR,Package_SO:TSSOP-8_4.4x3mm_P0.65mm,,
U42,1,TPS25810RVCR,TPS25810RVCR / USB-C source3A,Package_DFN_QFN:Texas_RVC0020A_WQFN-20-1EP_3x4mm_P0.5mm_EP1.6x2.6mm_ThermalVias,,
U43,1,ADS1115IDGSR,ADS1115IDGSR,Package_SO:MSOP-10_3x3mm_P0.5mm,,
U50,1,SN74LVC1G14DBVR,SN74LVC1G14,Package_TO_SOT_SMD:SOT-23-5,,

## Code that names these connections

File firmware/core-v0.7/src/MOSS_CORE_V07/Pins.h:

// SPDX-License-Identifier: Apache-2.0
#pragma once
namespace pins {
constexpr int ESTOP_ACTIVE = 4, ENC_R_A = 5, ENC_L_B = 6, ENC_L_A = 7,
              STATUS_LED = 15;
constexpr int ENC_R_B = 16, DIR_L = 17, PWM_L = 18, DIR_R = 8, PWM_R = 9;
constexpr int AUDIO_BCLK = 10, AUDIO_LRCLK = 11, AUDIO_DATA = 12,
              AUDIO_ENABLE = 13;
constexpr int USB_PWR_FAULT_N = 14, DRIVE_ENABLE = 21, WD_ENABLE = 47,
              WD_TICK = 48;
constexpr int SERVO_TX = 35, SERVO_TX_ENABLE = 36, SERVO_RX = 37;
constexpr int ACT_POWER_ENABLE = 38, ACT_READY = 39, I2C_SCL = 40, I2C_SDA = 41;
constexpr int ENC_POWER_EN = 42, DRIVE_RUN = 44, DEBUG_TX = 43, ARM_LATCHED = 2,
              ARM_COMMIT = 1;
constexpr int ESP_USB_N = 19, ESP_USB_P = 20, BOOT_N = 0;
} // namespace pins
